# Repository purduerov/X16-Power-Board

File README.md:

# Readme for X16-Power-Slab
This board turns 48V into 12 V and 5 V

Whenever you make a new part, download the datasheet and save it here _**and**_ with the part in the parts library

Always pull other people's changes before beginning to work
`git pull`

Be sure to push your changes after  working on them. Run:
1. `git add .` to add any files in this directory or a subdirectory
or `git add -u` to add any modified files
2. (Optional) `git clean -nX` to see what ignored files can be removed
	`git clean -fX` removes ignored files (Eagle backups)
3. `git commit -m "helpful commit message"` with a description of the work that you did
4. `git push` to push your work to github

Other helpful commands
* `git status` says information about modified and staged files
* `git log` shows the recent commits of the repository
* `git log filename.extension` show the recent commits for just that file
* `git checkout first-couple-letter-of-commit-id` lets you go back to a previous version
* `git checkout master` brings you back to the latest commit
* `git tag` lists the tags
* `git tag -a orderX -m "the version of the board placed for the X'th order"` tag a specific commit
* `git push --tags` needed to push tags to remote
* `git show orderX` show the commit log for the given tag
* `git checkout orderX` go back and interact with the files at the tagged commit

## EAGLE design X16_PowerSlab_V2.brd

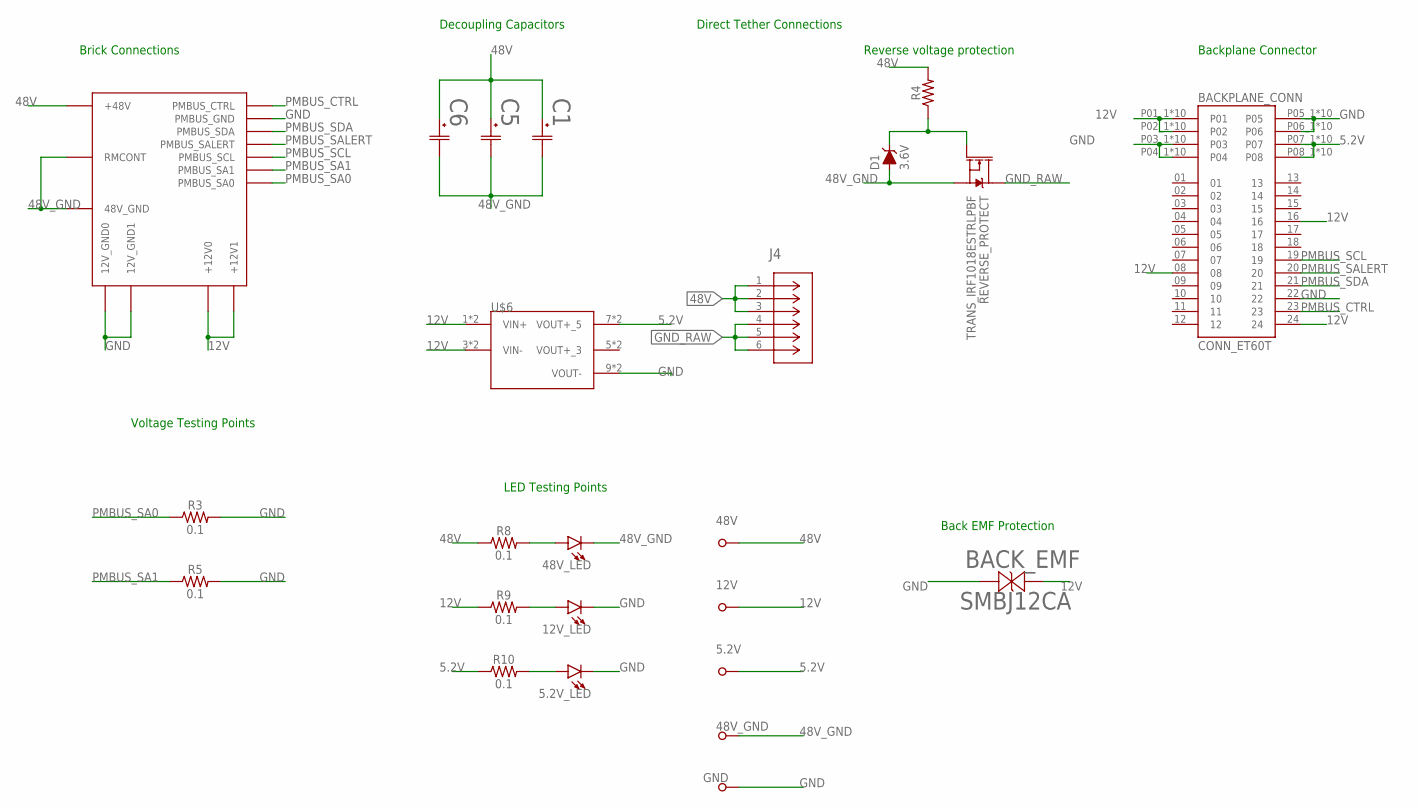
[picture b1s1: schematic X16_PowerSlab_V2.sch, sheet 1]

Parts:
5.2V, 12V, 48V_GND: TESTPOINT_5.04MM
5.2V_LED: 5.2V; CHIPLED_0805
12V_LED: 12V; CHIPLED_0805
48V: 48V; TESTPOINT_5.04MM
48V_LED: 48V; CHIPLED_0805
BACKPLANE_CONN: CONN_ET60T; SAMTEC_ET60T-D04-3-08-D04-X-R1-S
BACK_EMF: SMBJ12CA; SMBJSERIES_LTF
BMR480_POWERBRICK: CONN_BMR480_BRICK
C1, C5, C6: UCM1H331MNL1GS; CAP_UCD_10X10_NCH
D1: 3.6V; SOD-323
GND: TESTPOINT_5.04MM
J4: 796636-6; CON6_P5MM_VER_TERM-BLK_TYC
R3, R5, R8, R9, R10: 0.1; 0603
R4: 0603
REVERSE_PROTECT: TRANS_IRF1018ESTRLPBF; D2PAK
U$6: CONN_DISTRIBUTION_TO_CONVERSION; TSW-105-05-G-S(D-C)

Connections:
5.2V: 5.2V.TP, BACKPLANE_CONN.P07_1 (P07), BACKPLANE_CONN.P07_2 (P07), BACKPLANE_CONN.P07_3 (P07), BACKPLANE_CONN.P07_4 (P07), BACKPLANE_CONN.P07_5 (P07), BACKPLANE_CONN.P07_6 (P07), BACKPLANE_CONN.P07_7 (P07), BACKPLANE_CONN.P07_8 (P07), BACKPLANE_CONN.P07_9 (P07), BACKPLANE_CONN.P07_10 (P07), BACKPLANE_CONN.P08_1 (P08), BACKPLANE_CONN.P08_2 (P08), BACKPLANE_CONN.P08_3 (P08), BACKPLANE_CONN.P08_4 (P08), BACKPLANE_CONN.P08_5 (P08), BACKPLANE_CONN.P08_6 (P08), BACKPLANE_CONN.P08_7 (P08), BACKPLANE_CONN.P08_8 (P08), BACKPLANE_CONN.P08_9 (P08), BACKPLANE_CONN.P08_10 (P08), R10.1, U$6.7 (VOUT+_5), U$6.8 (VOUT+_5); also elsewhere on the board
12V: 12V.TP, BACKPLANE_CONN.08, BACKPLANE_CONN.16, BACKPLANE_CONN.24, BACKPLANE_CONN.P01_1 (P01), BACKPLANE_CONN.P01_2 (P01), BACKPLANE_CONN.P01_3 (P01), BACKPLANE_CONN.P01_4 (P01), BACKPLANE_CONN.P01_5 (P01), BACKPLANE_CONN.P01_6 (P01), BACKPLANE_CONN.P01_7 (P01), BACKPLANE_CONN.P01_8 (P01), BACKPLANE_CONN.P01_9 (P01), BACKPLANE_CONN.P01_10 (P01), BACKPLANE_CONN.P02_1 (P02), BACKPLANE_CONN.P02_2 (P02), BACKPLANE_CONN.P02_3 (P02), BACKPLANE_CONN.P02_4 (P02), BACKPLANE_CONN.P02_5 (P02), BACKPLANE_CONN.P02_6 (P02), BACKPLANE_CONN.P02_7 (P02), BACKPLANE_CONN.P02_8 (P02), BACKPLANE_CONN.P02_9 (P02), BACKPLANE_CONN.P02_10 (P02), BACK_EMF.1, BMR480_POWERBRICK.PIN7 (+12V1), BMR480_POWERBRICK.PIN8 (+12V0), R9.1, U$6.1 (VIN+), U$6.2 (VIN+), U$6.3 (VIN-), U$6.4 (VIN-); also elsewhere on the board
48V: 48V.TP, BMR480_POWERBRICK.PIN1 (+48V), C1.1, C5.1, C6.1, J4.1, J4.2, J4.3, R4.2, R8.1
48V_GND: 48V_GND.TP, 48V_LED.C, BMR480_POWERBRICK.PIN2 (RMCONT), BMR480_POWERBRICK.PIN3 (48V_GND), C1.2, C5.2, C6.2, D1.A, REVERSE_PROTECT.2 (S)
GND: 5.2V_LED.C, 12V_LED.C, BACKPLANE_CONN.22, BACKPLANE_CONN.P03_1 (P03), BACKPLANE_CONN.P03_2 (P03), BACKPLANE_CONN.P03_3 (P03), BACKPLANE_CONN.P03_4 (P03), BACKPLANE_CONN.P03_5 (P03), BACKPLANE_CONN.P03_6 (P03), BACKPLANE_CONN.P03_7 (P03), BACKPLANE_CONN.P03_8 (P03), BACKPLANE_CONN.P03_9 (P03), BACKPLANE_CONN.P03_10 (P03), BACKPLANE_CONN.P04_1 (P04), BACKPLANE_CONN.P04_2 (P04), BACKPLANE_CONN.P04_3 (P04), BACKPLANE_CONN.P04_4 (P04), BACKPLANE_CONN.P04_5 (P04), BACKPLANE_CONN.P04_6 (P04), BACKPLANE_CONN.P04_7 (P04), BACKPLANE_CONN.P04_8 (P04), BACKPLANE_CONN.P04_9 (P04), BACKPLANE_CONN.P04_10 (P04), BACKPLANE_CONN.P05_1 (P05), BACKPLANE_CONN.P05_2 (P05), BACKPLANE_CONN.P05_3 (P05), BACKPLANE_CONN.P05_4 (P05), BACKPLANE_CONN.P05_5 (P05), BACKPLANE_CONN.P05_6 (P05), BACKPLANE_CONN.P05_7 (P05), BACKPLANE_CONN.P05_8 (P05), BACKPLANE_CONN.P05_9 (P05), BACKPLANE_CONN.P05_10 (P05), BACKPLANE_CONN.P06_1 (P06), BACKPLANE_CONN.P06_2 (P06), BACKPLANE_CONN.P06_3 (P06), BACKPLANE_CONN.P06_4 (P06), BACKPLANE_CONN.P06_5 (P06), BACKPLANE_CONN.P06_6 (P06), BACKPLANE_CONN.P06_7 (P06), BACKPLANE_CONN.P06_8 (P06), BACKPLANE_CONN.P06_9 (P06), BACKPLANE_CONN.P06_10 (P06), BACK_EMF.2, BMR480_POWERBRICK.PIN4 (12V_GND1), BMR480_POWERBRICK.PIN5 (12V_GND0), BMR480_POWERBRICK.PIN10 (PMBUS_GND), GND.TP, R3.2, R5.2, U$6.9 (VOUT-), U$6.10 (VOUT-); also elsewhere on the board
GND_RAW: J4.4, J4.5, J4.6, REVERSE_PROTECT.3 (D)
unnamed: D1.C, R4.1, REVERSE_PROTECT.1 (G)
unnamed: 48V_LED.A, R8.2
unnamed: 12V_LED.A, R9.2
unnamed: 5.2V_LED.A, R10.2
PMBUS_CTRL: BACKPLANE_CONN.23, BMR480_POWERBRICK.PIN9 (PMBUS_CTRL)
PMBUS_SA0: BMR480_POWERBRICK.PIN15 (PMBUS_SA0), R3.1
PMBUS_SA1: BMR480_POWERBRICK.PIN14 (PMBUS_SA1), R5.1
PMBUS_SALERT: BACKPLANE_CONN.20, BMR480_POWERBRICK.PIN12 (PMBUS_SALERT)
PMBUS_SCL: BACKPLANE_CONN.19, BMR480_POWERBRICK.PIN13 (PMBUS_SCL)
PMBUS_SDA: BACKPLANE_CONN.21, BMR480_POWERBRICK.PIN11 (PMBUS_SDA)

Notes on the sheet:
Direct Tether Connections
Brick Connections
Reverse voltage protection
Backplane Connector
Voltage Testing Points
LED Testing Points
Back EMF Protection
Decoupling Capacitors

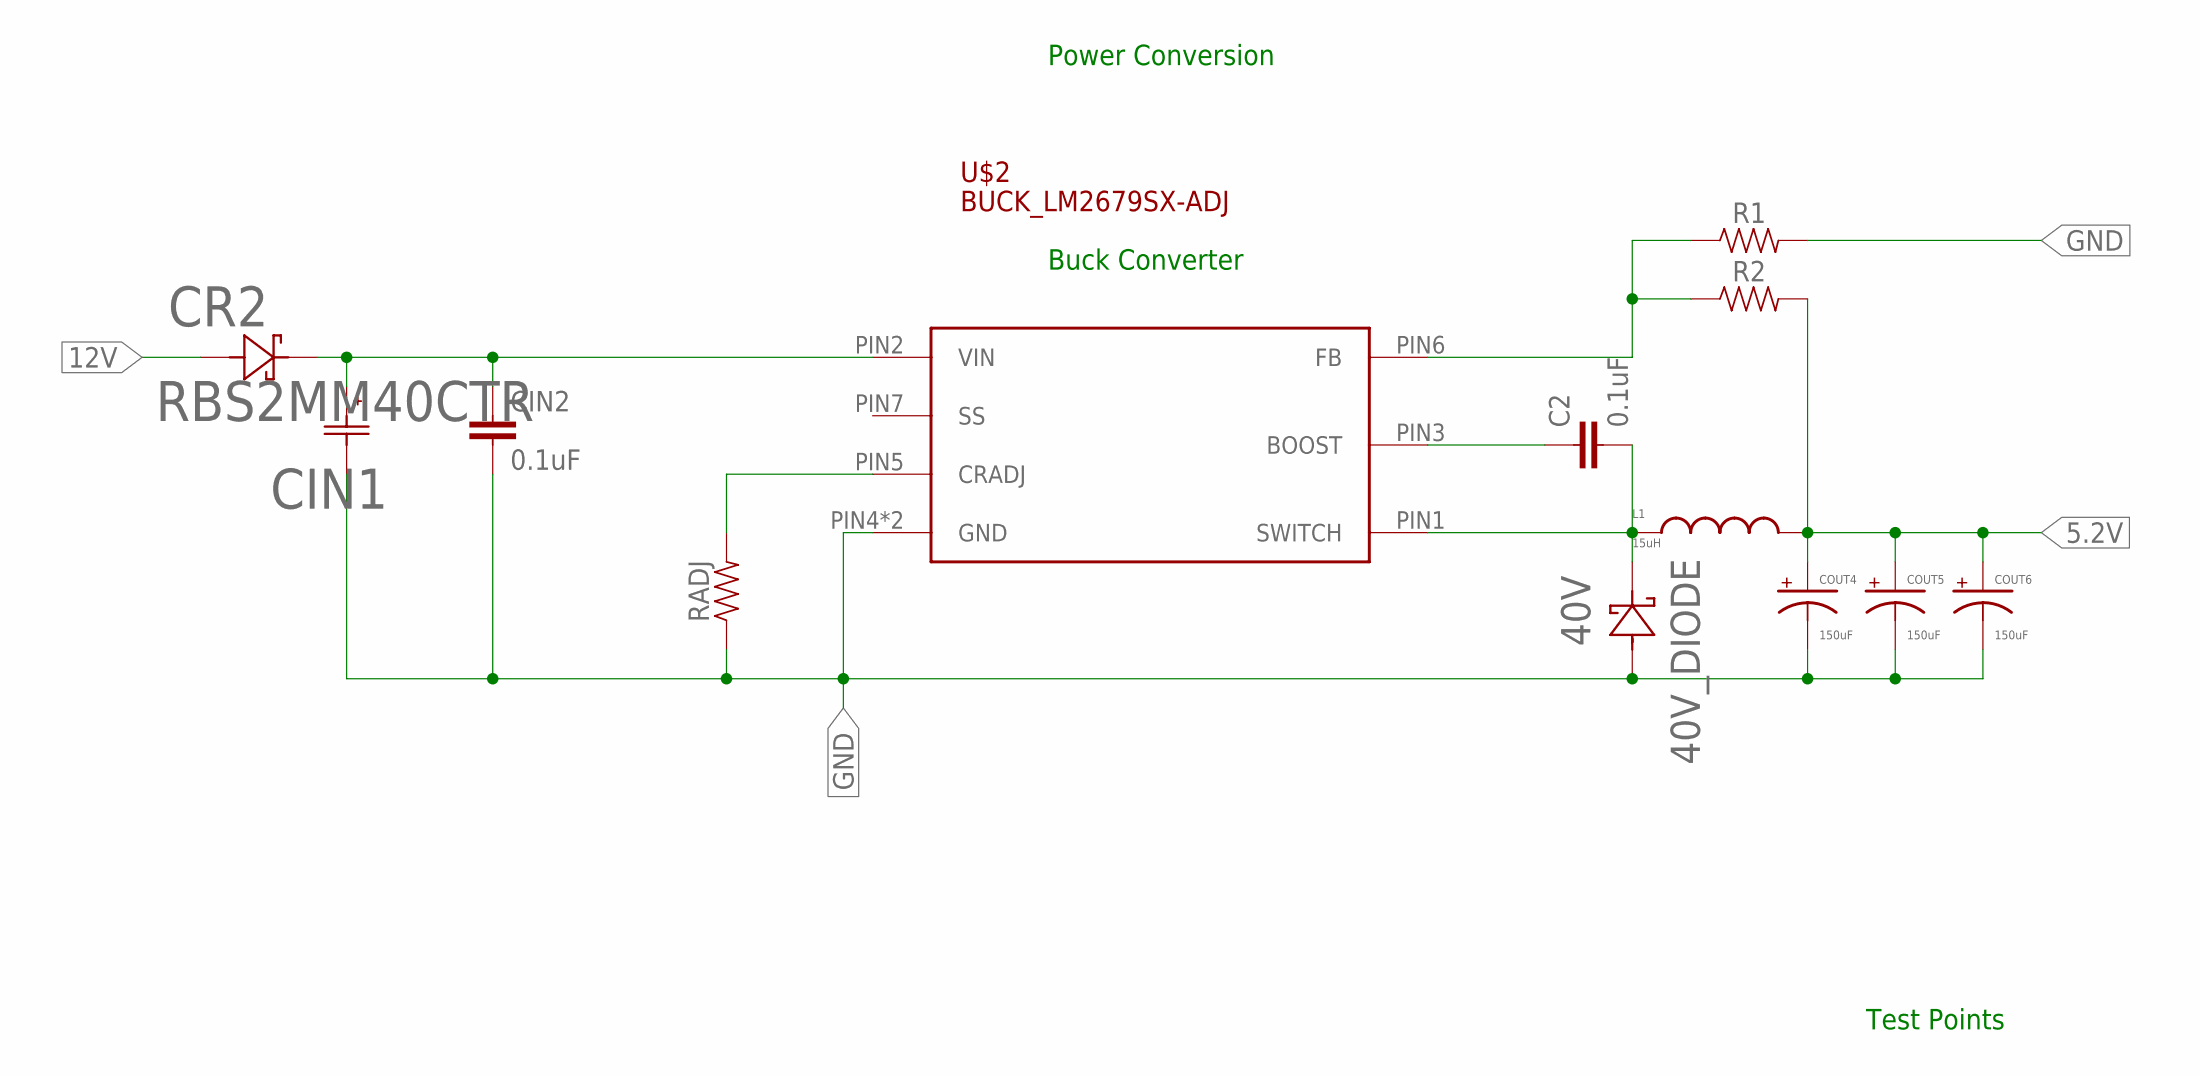
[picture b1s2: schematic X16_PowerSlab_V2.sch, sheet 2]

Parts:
40V_DIODE: 40V; DO214AC
C2: 0.1uF; 0603
CIN1: 594D187X0016R2T; CAP_X0016R2T_VIS
CIN2: 0.1uF; 0603
COUT4, COUT5, COUT6: 150uF; 2917(7343-31-METRIC)
CR2: RBS2MM40CTR; SDO_RBS2MM40CTR_ROM
L1: 15uH; HCMA1305
R1, R2: 0603
RADJ: 0603
U$2: BUCK_LM2679SX-ADJ; BUCK,LM2679SX-ADJ

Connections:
5.2V: COUT4.+, COUT5.+, COUT6.+, L1.2, R2.2; also elsewhere on the board
12V: CR2.2; also elsewhere on the board
GND: 40V_DIODE.A (2), CIN1.2, CIN2.2, COUT4.-, COUT5.-, COUT6.-, R1.2, RADJ.1, U$2.PIN4 (GND), U$2.PIN8 (GND); also elsewhere on the board
unnamed: C2.1, U$2.PIN3 (BOOST)
unnamed: 40V_DIODE.C (1), C2.2, L1.1, U$2.PIN1 (SWITCH)
unnamed: R1.1, R2.1, U$2.PIN6 (FB)
unnamed: RADJ.2, U$2.PIN5 (CRADJ)
VIN: CIN1.1, CIN2.1, CR2.1, U$2.PIN2 (VIN)

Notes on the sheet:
Power Conversion
Buck Converter
Test Points

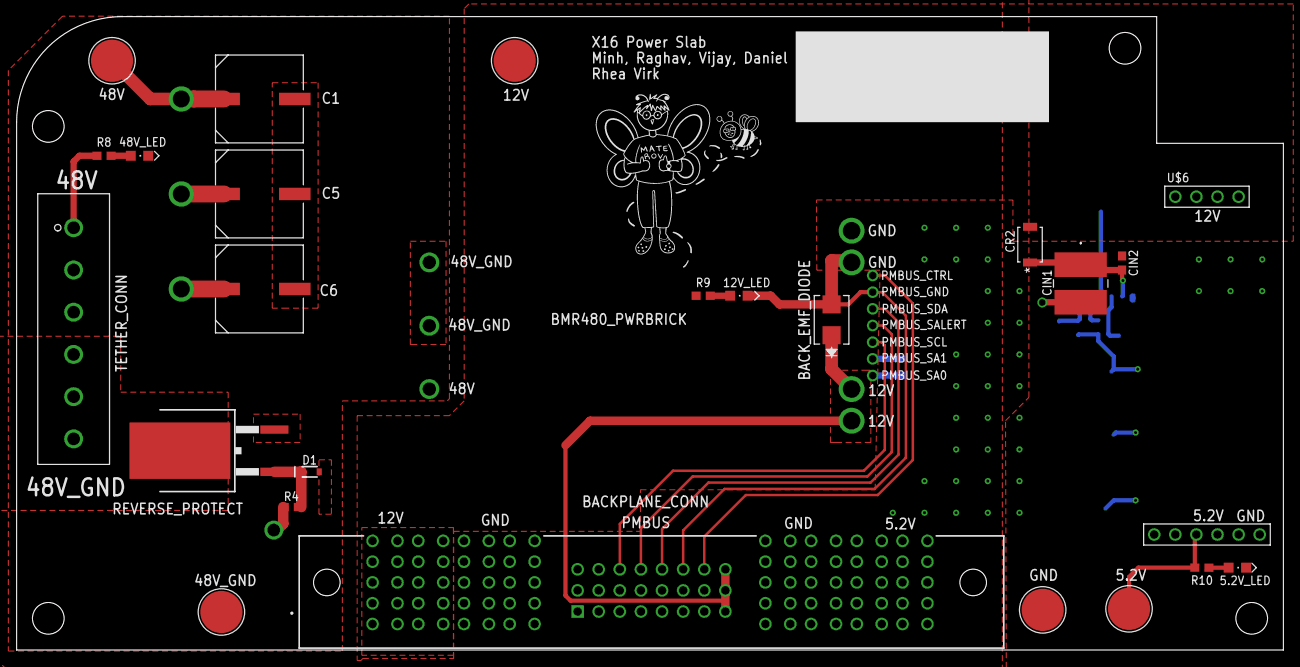
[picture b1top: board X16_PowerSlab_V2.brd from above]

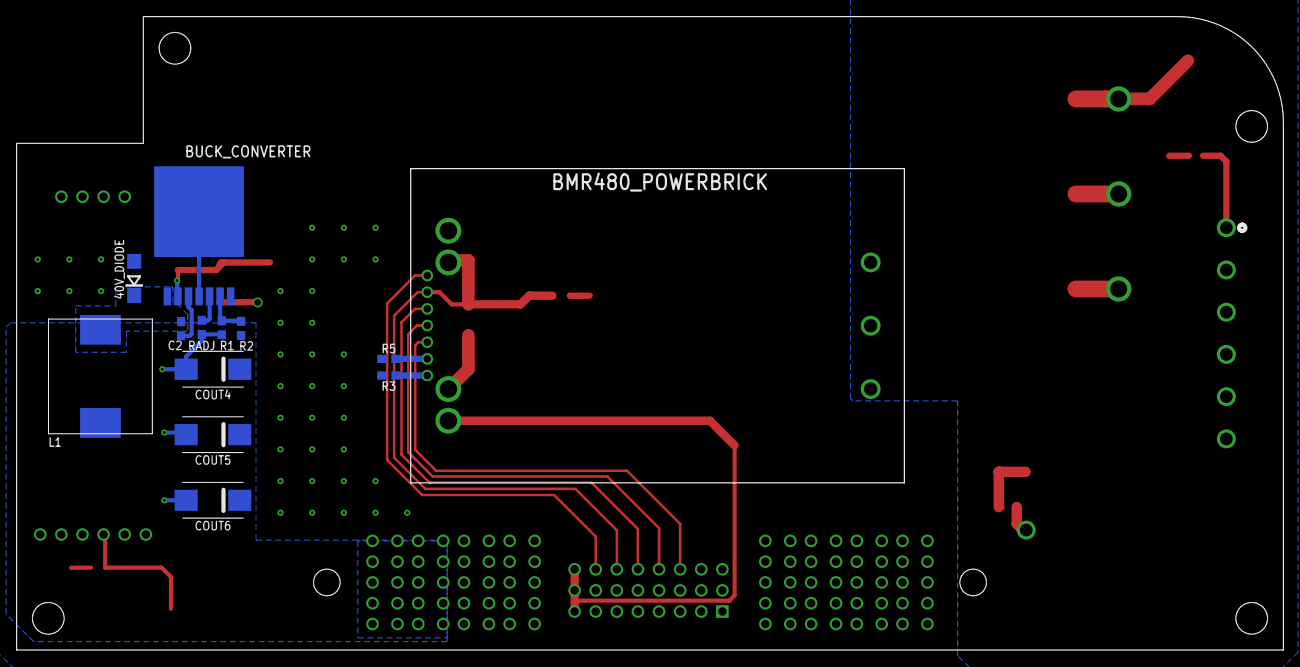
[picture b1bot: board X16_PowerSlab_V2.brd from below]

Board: 2 copper layers, 152.4 x 76.2 mm, 41 parts (17 on the bottom side), 21 nets.

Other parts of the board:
H1, H2, H3, H4: 6-32-HOLE

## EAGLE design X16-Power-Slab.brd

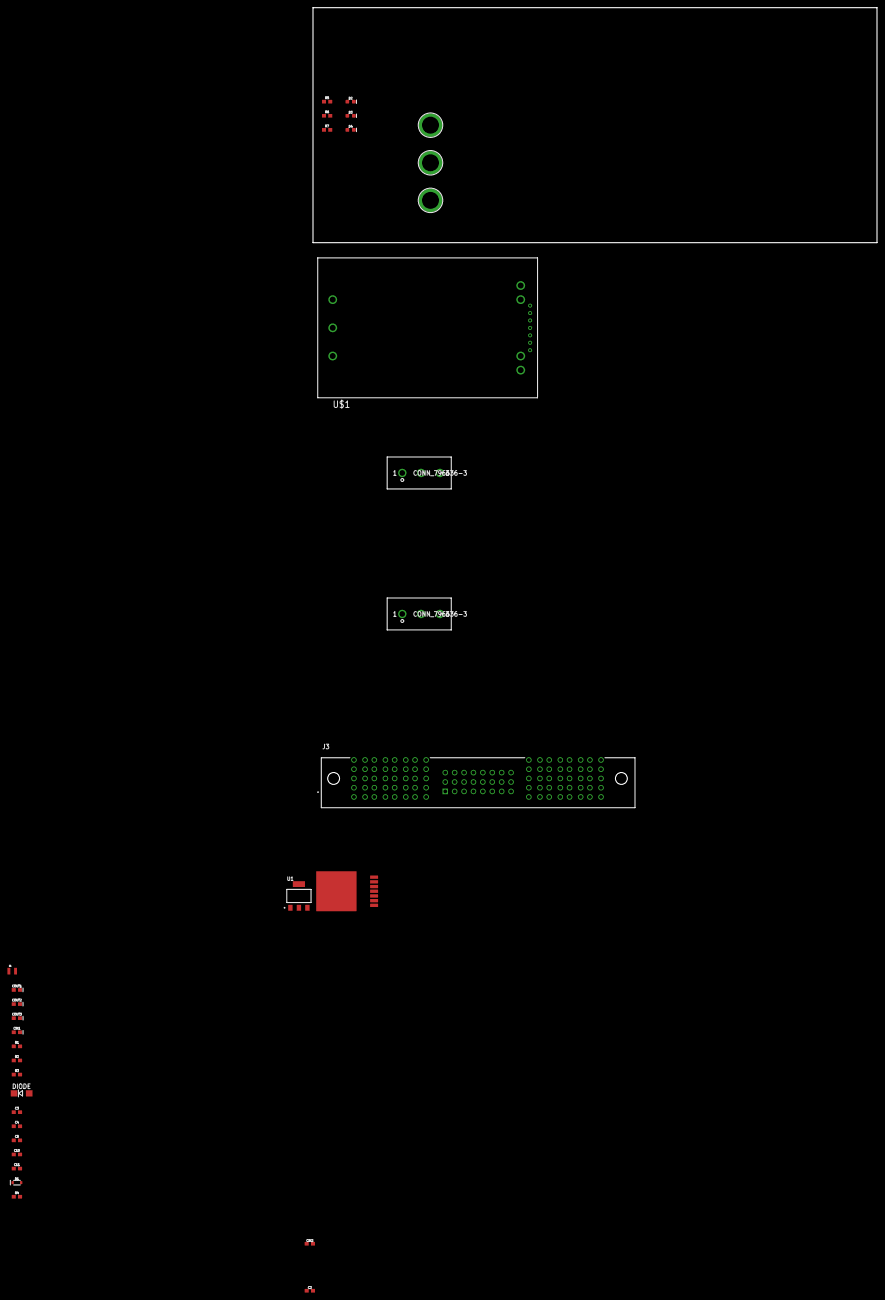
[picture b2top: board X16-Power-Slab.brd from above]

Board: 2 copper layers, 152.4 x 63.5 mm, 33 parts (0 on the bottom side), 21 nets, no tracks yet.

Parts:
C2: 0.01uF; 0603
C3: 10uF; 0603
C4: 22uF; 0603
C5, C10, C11: 0.1uF; 0603
CIN1: 180uF; 0603-POLAR
CIN2: 0.47uF; 0603
COUT1, COUT2, COUT3: 150uF; 0603-POLAR
D1: 3.6V; SOD-323
D2: 12V; LED-0603
D3: 5.2V; LED-0603
D4: 3.3V; LED-0603
DIODE: 40V; DO214AC
J1, J2: CONN_796636-3
J3: CONN_ET60T; SAMTEC_ET60T-D04-3-08-D04-X-R1-S
L1: 15uH; 0806
R1: 1k; 0603
R2: 3.32k; 0603
R3: 12.4k; 0603
R4: 0603
R5: 600; 0603
R6: 300; 0603
R7: 200; 0603
U1: LINEAR_AZ1117CR-3.3TRG1DIODES_AZ1117CH-3.3TRG1_0_0; LINEAR_AZ1117CR-3.3TRG1
U$1: CONN_BMR480_BRICK
U$2: BUCK_LM2679SX-ADJ; BUCK,LM2679SX-ADJ
U$3: 3.3V_TESTPOINT
U$4: 5.2V_TESTPOINT
U$5: 12V_TESTPOINT

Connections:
5.2V/2.1A: COUT1.+, COUT2.+, COUT3.+, L1.2, R2.2
12V/2.1A: CIN1.+, CIN2.1, U$2.PIN2
48V: J1.1, J1.2, J1.3
GND: J2.1, J2.2, J2.3, R1.2
GND/2.2D: CIN1.-, CIN2.2, COUT1.-, COUT2.-, COUT3.-, DIODE.A, R3.1, U$2.PIN4, U$2.PIN8
unnamed: C2.1, U$2.PIN3
unnamed: C2.2, DIODE.C, L1.1, U$2.PIN1
unnamed: C3.1, U1.3
unnamed: R1.1, R2.1, U$2.PIN6
unnamed: C4.1, U1.2, U1.4
unnamed: R3.2, U$2.PIN5
unnamed: C5.1, C10.1, C11.1
unnamed: C5.2, C10.2, C11.2
P01: J3.P01_1, J3.P01_2, J3.P01_3, J3.P01_4, J3.P01_5, J3.P01_6, J3.P01_7, J3.P01_8, J3.P01_9, J3.P01_10
P02: J3.P02_1, J3.P02_2, J3.P02_3, J3.P02_4, J3.P02_5, J3.P02_6, J3.P02_7, J3.P02_8, J3.P02_9, J3.P02_10
P03: J3.P03_1, J3.P03_2, J3.P03_3, J3.P03_4, J3.P03_5, J3.P03_6, J3.P03_7, J3.P03_8, J3.P03_9, J3.P03_10
P04: J3.P04_1, J3.P04_2, J3.P04_3, J3.P04_4, J3.P04_5, J3.P04_6, J3.P04_7, J3.P04_8, J3.P04_9, J3.P04_10
P05: J3.P05_1, J3.P05_2, J3.P05_3, J3.P05_4, J3.P05_5, J3.P05_6, J3.P05_7, J3.P05_8, J3.P05_9, J3.P05_10
P06: J3.P06_1, J3.P06_2, J3.P06_3, J3.P06_4, J3.P06_5, J3.P06_6, J3.P06_7, J3.P06_8, J3.P06_9, J3.P06_10
P07: J3.P07_1, J3.P07_2, J3.P07_3, J3.P07_4, J3.P07_5, J3.P07_6, J3.P07_7, J3.P07_8, J3.P07_9, J3.P07_10
P08: J3.P08_1, J3.P08_2, J3.P08_3, J3.P08_4, J3.P08_5, J3.P08_6, J3.P08_7, J3.P08_8, J3.P08_9, J3.P08_10

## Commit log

2023-08-30 Board Outline
2023-08-30 changed dimensions
2023-09-23 Added .gitignore file
2023-10-05 Buck converter added
2023-10-11 Power Conversion finished, updated Brickstribution
2023-10-11 Updated component values, added test points
2023-10-18 Updated reverse voltage protection
2023-10-18 Added testpoints, fixed some errors with values
2023-10-19 schematic finished
2023-10-19 Fixed area of board
2023-10-21 Started placing components on board
2023-11-04 Started placing board components
2023-11-04 all components laid out
2023-11-09 Added big test points
2023-11-11 Added Power Conversion to Brickstribution connector
2023-11-11 set up polygons
2023-11-15 worked on routing
2023-11-16 updated routing
2023-11-17 routing, fixed outdated components
2023-11-17 updated board
2023-11-18 finished polygons
2023-11-29 deleted v1
2023-12-07 Followed video, few discrepancies
2023-12-07 Board finished; ran DRC
2023-12-20 Labels added
2023-12-20 fixed a resistor value
2023-12-20 Minh Update
2023-12-20 Minh Update 2
2023-12-22 Minh Update 3
2023-12-23 Removed the traces, and placed the address resistors.
2023-12-23 Minh update 4
2023-12-29 Minh Update 5
2023-12-29 Minh Update 6
2023-12-29 Minh Update 7
2024-01-04 Minh Update 8

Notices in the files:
parts and their libraries:
SparkFun-Capacitors: Licensing: Creative Commons ShareAlike 4.0 International - https://creativecommons.org/licenses/by-sa/4.0
COPYRIGHT: Copyright (C) 2022 Ultra Librarian. All rights reserved.
COPYRIGHT: Copyright (C) 2023 Ultra Librarian. All rights reserved.
